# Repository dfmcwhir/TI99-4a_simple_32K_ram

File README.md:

# TI99-4a_simple_32K_ram
A 32k ram module for the TI99/4a using through hole components<br>
<br>
It is a through hole version of the 32K expansion module found here:
https://oshwlab.com/yannick.erb/ti99-32k-ram

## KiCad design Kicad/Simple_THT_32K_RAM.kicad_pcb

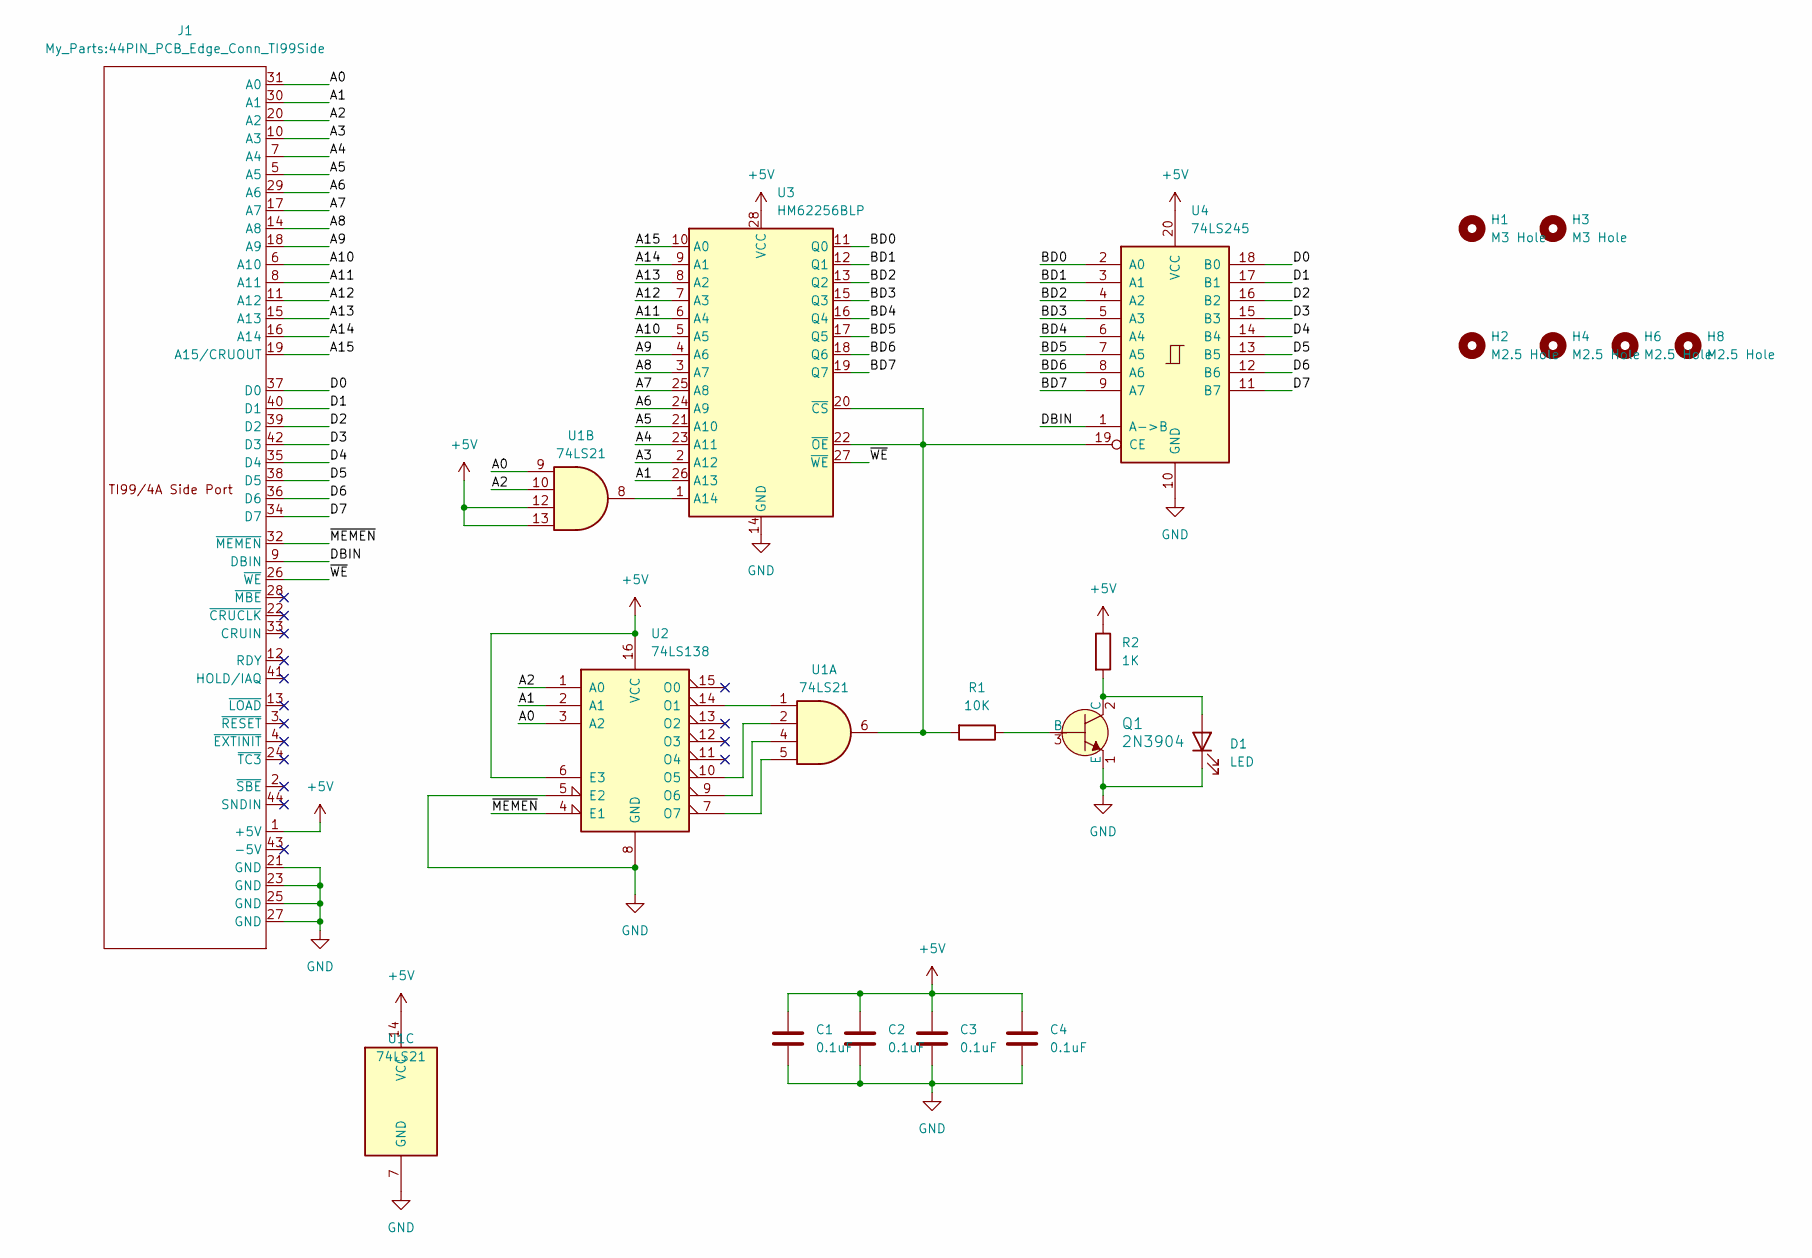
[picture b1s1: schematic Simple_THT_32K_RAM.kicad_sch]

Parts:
C1, C2, C3, C4: 0.1uF; C_Disc_D5.0mm_W2.5mm_P5.00mm
D1: LED; LED_D3.0mm
H1, H3: M3 Hole; MountingHole_3.2mm_M3
H2, H4, H6, H8: M2.5 Hole; MountingHole_2.7mm_M2.5
J1: 44PIN_PCB_Edge_Conn_TI99Side
Q1: 2N3904; TO-92-3_Formed_Leads; MPN 2N3904; Digi-Key_PN 2N3904CS-ND
R1: 10K; R_Axial_DIN0204_L3.6mm_D1.6mm_P7.62mm_Horizontal
R2: 1K; R_Axial_DIN0204_L3.6mm_D1.6mm_P7.62mm_Horizontal
U1: 74LS21; DIP-14_W7.62mm
U2: 74LS138; DIP-16_W7.62mm
U3: HM62256BLP; DIP-28_W15.24mm
U4: 74LS245; DIP-20_W7.62mm

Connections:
+5V: C1.1, C2.1, C3.1, C4.1, J1.1 (+5V), R2.1, U1.12, U1.13, U1.14 (VCC), U2.6 (E3), U2.16 (VCC), U3.28 (VCC), U4.20 (VCC)
/A0: J1.31 (A0), U1.9, U2.3 (A2)
/A1: J1.30 (A1), U2.2 (A1), U3.26 (A13)
/A2: J1.20 (A2), U1.10, U2.1 (A0)
/A3: J1.10 (A3), U3.2 (A12)
/A4: J1.7 (A4), U3.23 (A11)
/A5: J1.5 (A5), U3.21 (A10)
/A6: J1.29 (A6), U3.24 (A9)
/A7: J1.17 (A7), U3.25 (A8)
/A8: J1.14 (A8), U3.3 (A7)
/A9: J1.18 (A9), U3.4 (A6)
/A10: J1.6 (A10), U3.5 (A5)
/A11: J1.8 (A11), U3.6 (A4)
/A12: J1.11 (A12), U3.7 (A3)
/A13: J1.15 (A13), U3.8 (A2)
/A14: J1.16 (A14), U3.9 (A1)
/A15: J1.19 (A15/CRUOUT), U3.10 (A0)
/BD0: U3.11 (Q0), U4.2 (A0)
/BD1: U3.12 (Q1), U4.3 (A1)
/BD2: U3.13 (Q2), U4.4 (A2)
/BD3: U3.15 (Q3), U4.5 (A3)
/BD4: U3.16 (Q4), U4.6 (A4)
/BD5: U3.17 (Q5), U4.7 (A5)
/BD6: U3.18 (Q6), U4.8 (A6)
/BD7: U3.19 (Q7), U4.9 (A7)
/D0: J1.37 (D0), U4.18 (B0)
/D1: J1.40 (D1), U4.17 (B1)
/D2: J1.39 (D2), U4.16 (B2)
/D3: J1.42 (D3), U4.15 (B3)
/D4: J1.35 (D4), U4.14 (B4)
/D5: J1.38 (D5), U4.13 (B5)
/D6: J1.36 (D6), U4.12 (B6)
/D7: J1.34 (D7), U4.11 (B7)
/DBIN: J1.9 (DBIN), U4.1 (A->B)
/~MEMEN: J1.32 (~MEMEN), U2.4 (E1)
/~WE: J1.26 (~WE), U3.27 (~WE)
GND: C1.2, C2.2, C3.2, C4.2, D1.1 (K), J1.21 (GND), J1.23 (GND), J1.25 (GND), J1.27 (GND), Q1.1 (E), U1.7 (GND), U2.5 (E2), U2.8 (GND), U3.14 (GND), U4.10 (GND)
unnamed: D1.2 (A), Q1.2 (C), R2.2
unnamed: Q1.3 (B), R1.1
unnamed: U1.1, U2.14 (O1)
unnamed: U1.2, U2.10 (O5)
unnamed: U1.4, U2.9 (O6)
unnamed: U1.5, U2.7 (O7)
unnamed: U1.8, U3.1 (A14)
unnamed: R1.2, U1.6, U3.20 (~CS), U3.22 (~OE), U4.19 (CE)

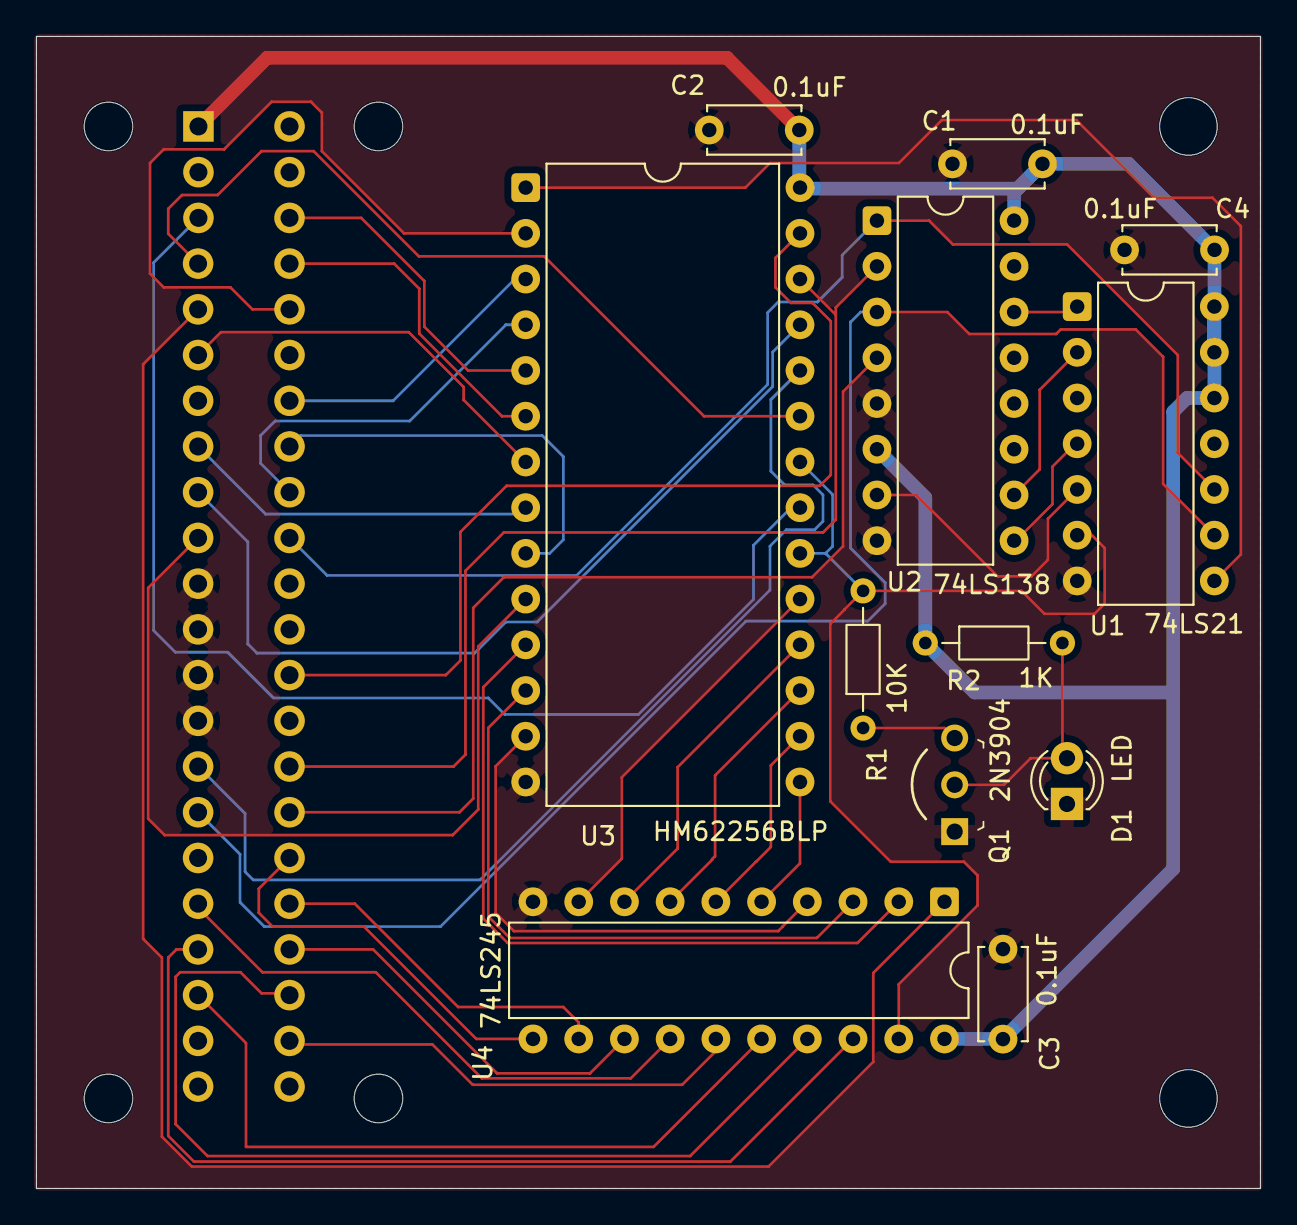
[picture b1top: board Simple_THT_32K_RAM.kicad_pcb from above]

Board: 2 copper layers, 68.0 x 64.0 mm, 19 parts (1 on the bottom side), 45 nets.
